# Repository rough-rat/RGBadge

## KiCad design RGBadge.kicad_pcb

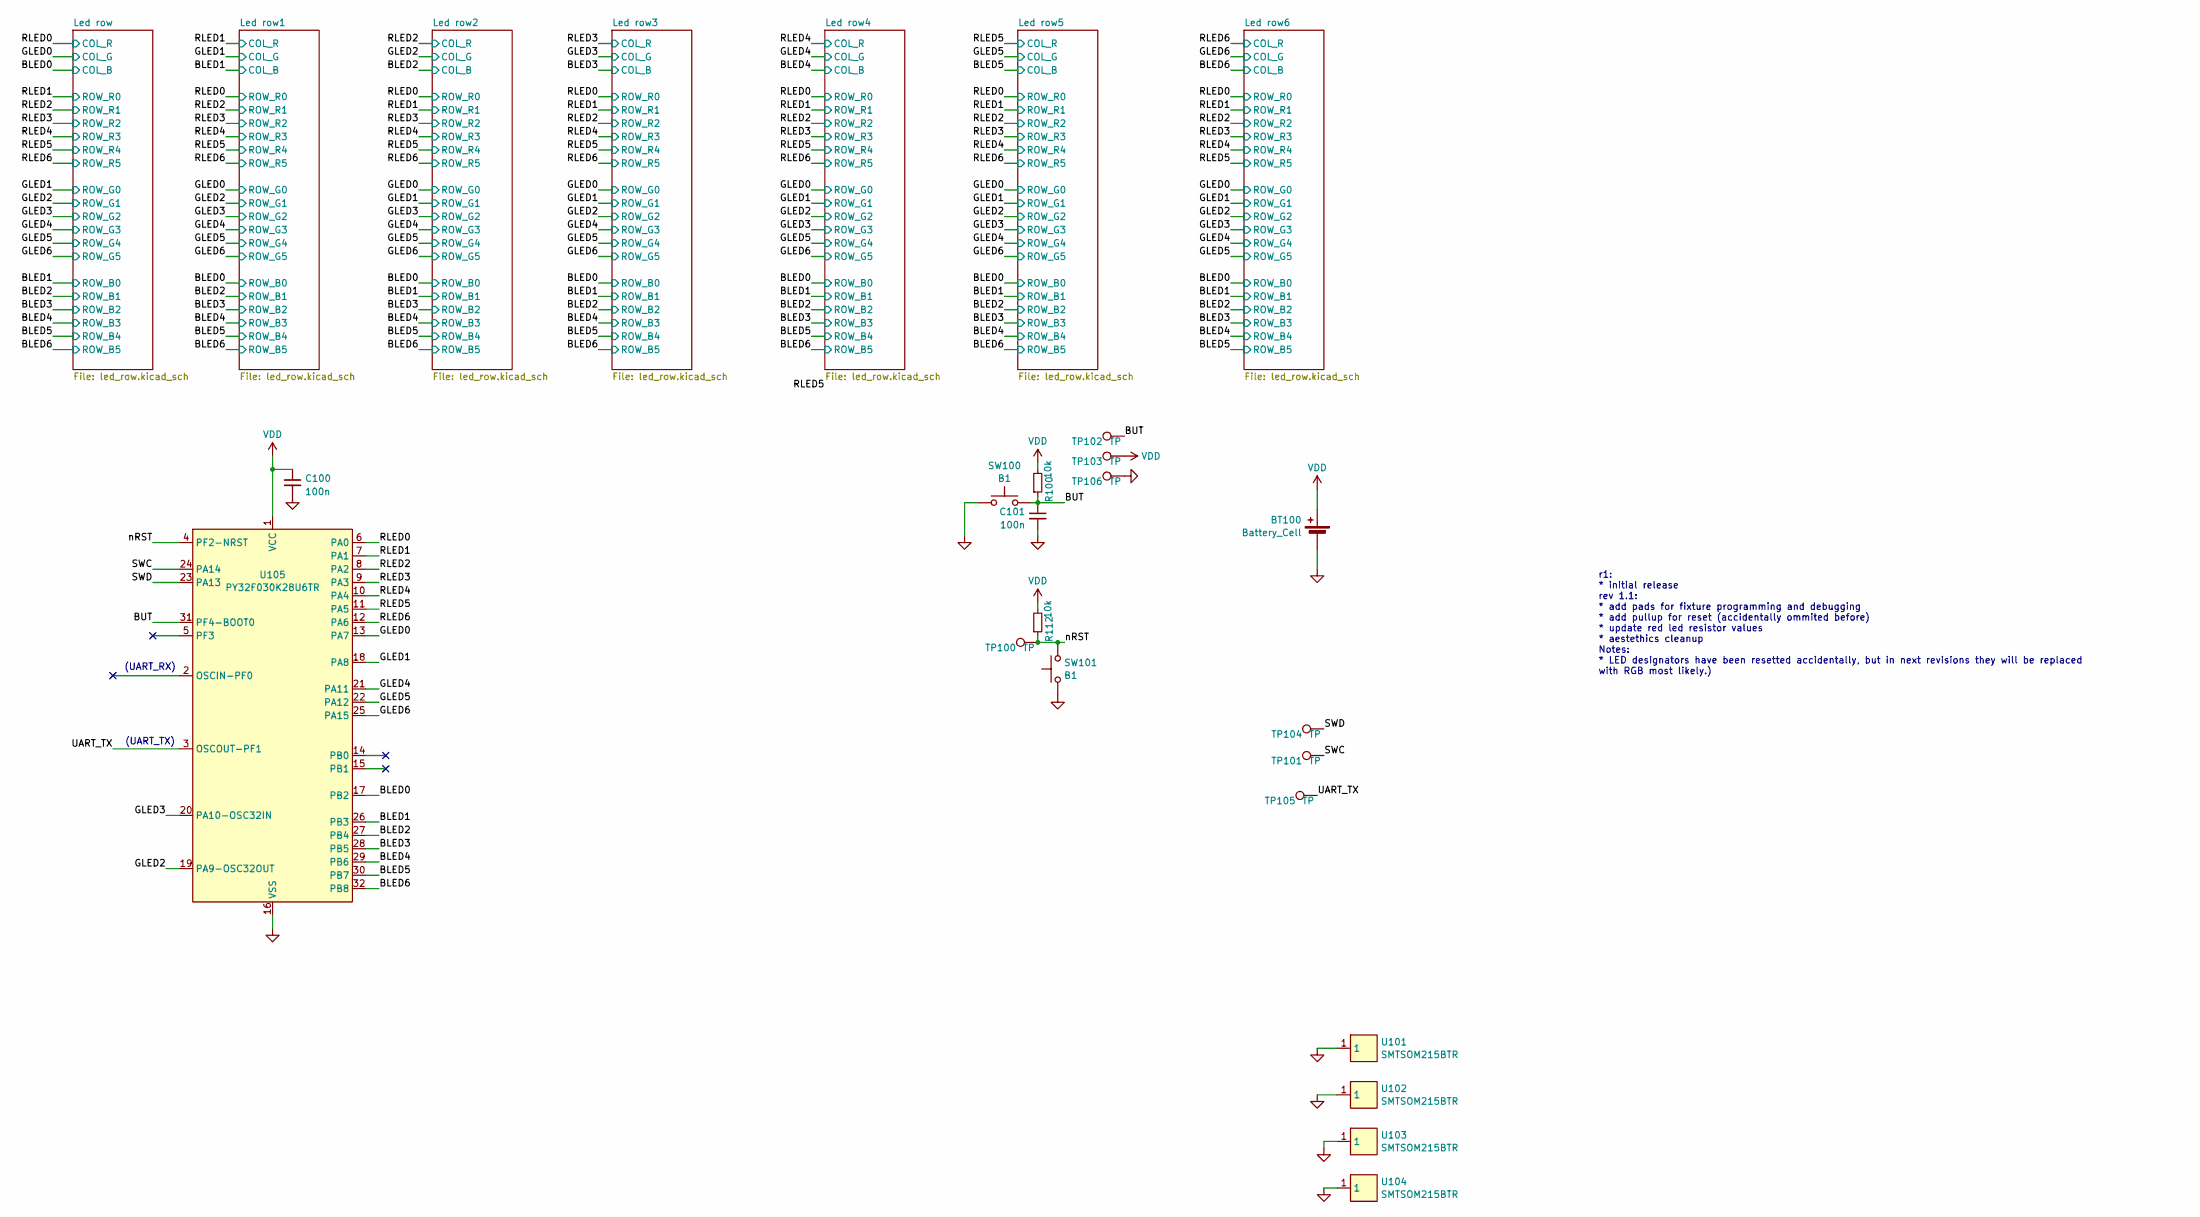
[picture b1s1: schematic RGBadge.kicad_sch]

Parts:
BT100: Battery_Cell; BatteryHolder_Keystone_1060_1x2032; LCSC DNP
C100, C101: 100n; C_0402_1005Metric; LCSC C1525
R100, R112: 10k; R_0402_1005Metric; LCSC C25744
SW100, SW101: B1; SW_SPST_FSMSM; LCSC DNP
TP100, TP101, TP102, TP103, TP104, TP105, TP106: TP; TestPoint_Pad_D1.0mm; LCSC DNP
U101, U102, U103, U104: SMTSOM215BTR; SMD_BD5.6-D3.6; LCSC C5301777
U105: PY32F030K28U6TR; QFN-32_L5.0-W5.0-P0.50-TL-EP3.5; LCSC Part C3018718

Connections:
/BLED0: U105.17 (PB2); also elsewhere on the board
/BLED1: U105.26 (PB3); also elsewhere on the board
/BLED2: U105.27 (PB4); also elsewhere on the board
/BLED3: U105.28 (PB5); also elsewhere on the board
/BLED4: U105.29 (PB6); also elsewhere on the board
/BLED5: U105.30 (PB7); also elsewhere on the board
/BLED6: U105.32 (PB8); also elsewhere on the board
/BUT: C101.1, R100.1, SW100.2, TP102.1 (1_1), U105.31 (PF4-BOOT0)
/GLED0: U105.13 (PA7); also elsewhere on the board
/GLED1: U105.18 (PA8); also elsewhere on the board
/GLED2: U105.19 (PA9-OSC32OUT); also elsewhere on the board
/GLED3: U105.20 (PA10-OSC32IN); also elsewhere on the board
/GLED4: U105.21 (PA11); also elsewhere on the board
/GLED5: U105.22 (PA12); also elsewhere on the board
/GLED6: U105.25 (PA15); also elsewhere on the board
/RLED0: U105.6 (PA0); also elsewhere on the board
/RLED1: U105.7 (PA1); also elsewhere on the board
/RLED2: U105.8 (PA2); also elsewhere on the board
/RLED3: U105.9 (PA3); also elsewhere on the board
/RLED4: U105.10 (PA4); also elsewhere on the board
/RLED5: U105.11 (PA5); also elsewhere on the board
/RLED6: U105.12 (PA6); also elsewhere on the board
/SWC: TP101.1 (1_1), U105.24 (PA14)
/SWD: TP104.1 (1_1), U105.23 (PA13)
/UART_TX: TP105.1 (1_1), U105.3 (OSCOUT-PF1)
/nRST: R112.1, SW101.2, TP100.1 (1_1), U105.4 (PF2-NRST)
GND: BT100.2 (-), C100.2, C101.2, SW100.1, SW101.1, TP106.1 (1_1), U101.1 (1_1), U102.1 (1_1), U103.1 (1_1), U104.1 (1_1), U105.16 (VSS), U105.33 (VSS)
VDD: BT100.1 (+), C100.1, R100.2, R112.2, TP103.1 (1_1), U105.1 (VCC)

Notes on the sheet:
(UART_RX)
(UART_TX)
r1: * initial release rev 1.1: * add pads for fixture programming and debugging * add pullup for reset (accidentally ommited before) * update red led resistor values * aestethics cleanup Notes: * LED designators have been resetted accidentally, but in next revisions they will be replaced with RGB m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

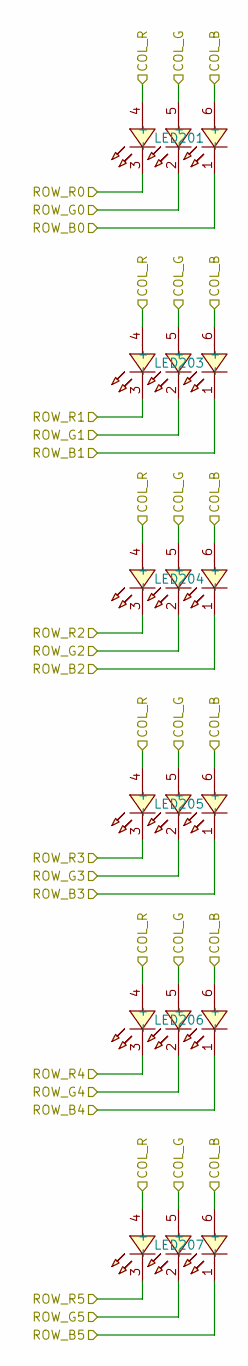
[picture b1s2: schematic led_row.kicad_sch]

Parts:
LED201, LED203, LED204, LED205, LED206, LED207: FM-Z2727RGBA-SH; LED-SMD_6P-L2.7-W2.8-TL; LCSC Part C727905

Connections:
/BLED0: LED201.6 (+), LED203.6 (+), LED204.6 (+), LED205.6 (+), LED206.6 (+), LED207.6 (+); also elsewhere on the board
/BLED1: LED201.1 (-); also elsewhere on the board
/BLED2: LED203.1 (-); also elsewhere on the board
/BLED3: LED204.1 (-); also elsewhere on the board
/BLED4: LED205.1 (-); also elsewhere on the board
/BLED5: LED206.1 (-); also elsewhere on the board
/BLED6: LED207.1 (-); also elsewhere on the board
/GLED0: LED201.5 (+), LED203.5 (+), LED204.5 (+), LED205.5 (+), LED206.5 (+), LED207.5 (+); also elsewhere on the board
/GLED1: LED201.2 (-); also elsewhere on the board
/GLED2: LED203.2 (-); also elsewhere on the board
/GLED3: LED204.2 (-); also elsewhere on the board
/GLED4: LED205.2 (-); also elsewhere on the board
/GLED5: LED206.2 (-); also elsewhere on the board
/GLED6: LED207.2 (-); also elsewhere on the board
/RLED0: LED201.4 (+), LED203.4 (+), LED204.4 (+), LED205.4 (+), LED206.4 (+), LED207.4 (+); also elsewhere on the board
/RLED1: LED201.3 (-); also elsewhere on the board
/RLED2: LED203.3 (-); also elsewhere on the board
/RLED3: LED204.3 (-); also elsewhere on the board
/RLED4: LED205.3 (-); also elsewhere on the board
/RLED5: LED206.3 (-); also elsewhere on the board
/RLED6: LED207.3 (-); also elsewhere on the board

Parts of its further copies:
LED301, LED302, LED303, LED304, LED305, LED306, LED307, LED308, LED309, LED310, LED311, LED312, LED313, LED314, LED315, LED316, LED317, LED318, LED601, LED602, LED603, LED604, LED605, LED606, LED607, LED608, LED609, LED610, LED611, LED612, LED701, LED702, LED703, LED704, LED705, LED706: FM-Z2727RGBA-SH; LED-SMD_6P-L2.7-W2.8-TL; LCSC Part C727905

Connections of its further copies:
/BLED0: LED301.1 (-), LED307.1 (-), LED313.1 (-), LED601.1 (-), LED607.1 (-), LED701.1 (-); also elsewhere on the board
/BLED1: LED301.6 (+), LED302.6 (+), LED303.6 (+), LED304.6 (+), LED305.6 (+), LED306.6 (+), LED308.1 (-), LED314.1 (-), LED602.1 (-), LED608.1 (-), LED702.1 (-); also elsewhere on the board
/BLED2: LED302.1 (-), LED307.6 (+), LED308.6 (+), LED309.6 (+), LED310.6 (+), LED311.6 (+), LED312.6 (+), LED315.1 (-), LED603.1 (-), LED609.1 (-), LED703.1 (-); also elsewhere on the board
/BLED3: LED303.1 (-), LED309.1 (-), LED313.6 (+), LED314.6 (+), LED315.6 (+), LED316.6 (+), LED317.6 (+), LED318.6 (+), LED604.1 (-), LED610.1 (-), LED704.1 (-); also elsewhere on the board
/BLED4: LED304.1 (-), LED310.1 (-), LED316.1 (-), LED601.6 (+), LED602.6 (+), LED603.6 (+), LED604.6 (+), LED605.6 (+), LED606.6 (+), LED611.1 (-), LED705.1 (-); also elsewhere on the board
/BLED5: LED305.1 (-), LED311.1 (-), LED317.1 (-), LED605.1 (-), LED607.6 (+), LED608.6 (+), LED609.6 (+), LED610.6 (+), LED611.6 (+), LED612.6 (+), LED706.1 (-); also elsewhere on the board
/BLED6: LED306.1 (-), LED312.1 (-), LED318.1 (-), LED606.1 (-), LED612.1 (-), LED701.6 (+), LED702.6 (+), LED703.6 (+), LED704.6 (+), LED705.6 (+), LED706.6 (+); also elsewhere on the board
/GLED0: LED301.2 (-), LED307.2 (-), LED313.2 (-), LED601.2 (-), LED607.2 (-), LED701.2 (-); also elsewhere on the board
/GLED1: LED301.5 (+), LED302.5 (+), LED303.5 (+), LED304.5 (+), LED305.5 (+), LED306.5 (+), LED308.2 (-), LED314.2 (-), LED602.2 (-), LED608.2 (-), LED702.2 (-); also elsewhere on the board
/GLED2: LED302.2 (-), LED307.5 (+), LED308.5 (+), LED309.5 (+), LED310.5 (+), LED311.5 (+), LED312.5 (+), LED315.2 (-), LED603.2 (-), LED609.2 (-), LED703.2 (-); also elsewhere on the board
/GLED3: LED303.2 (-), LED309.2 (-), LED313.5 (+), LED314.5 (+), LED315.5 (+), LED316.5 (+), LED317.5 (+), LED318.5 (+), LED604.2 (-), LED610.2 (-), LED704.2 (-); also elsewhere on the board
/GLED4: LED304.2 (-), LED310.2 (-), LED316.2 (-), LED601.5 (+), LED602.5 (+), LED603.5 (+), LED604.5 (+), LED605.5 (+), LED606.5 (+), LED611.2 (-), LED705.2 (-); also elsewhere on the board
/GLED5: LED305.2 (-), LED311.2 (-), LED317.2 (-), LED605.2 (-), LED607.5 (+), LED608.5 (+), LED609.5 (+), LED610.5 (+), LED611.5 (+), LED612.5 (+), LED706.2 (-); also elsewhere on the board
/GLED6: LED306.2 (-), LED312.2 (-), LED318.2 (-), LED606.2 (-), LED612.2 (-), LED701.5 (+), LED702.5 (+), LED703.5 (+), LED704.5 (+), LED705.5 (+), LED706.5 (+); also elsewhere on the board
/RLED0: LED301.3 (-), LED307.3 (-), LED313.3 (-), LED601.3 (-), LED607.3 (-), LED701.3 (-); also elsewhere on the board
/RLED1: LED301.4 (+), LED302.4 (+), LED303.4 (+), LED304.4 (+), LED305.4 (+), LED306.4 (+), LED308.3 (-), LED314.3 (-), LED602.3 (-), LED608.3 (-), LED702.3 (-); also elsewhere on the board
/RLED2: LED302.3 (-), LED307.4 (+), LED308.4 (+), LED309.4 (+), LED310.4 (+), LED311.4 (+), LED312.4 (+), LED315.3 (-), LED603.3 (-), LED609.3 (-), LED703.3 (-); also elsewhere on the board
/RLED3: LED303.3 (-), LED309.3 (-), LED313.4 (+), LED314.4 (+), LED315.4 (+), LED316.4 (+), LED317.4 (+), LED318.4 (+), LED604.3 (-), LED610.3 (-), LED704.3 (-); also elsewhere on the board
/RLED4: LED304.3 (-), LED310.3 (-), LED316.3 (-), LED601.4 (+), LED602.4 (+), LED603.4 (+), LED604.4 (+), LED605.4 (+), LED606.4 (+), LED611.3 (-), LED705.3 (-); also elsewhere on the board
/RLED5: LED305.3 (-), LED311.3 (-), LED317.3 (-), LED605.3 (-), LED607.4 (+), LED608.4 (+), LED609.4 (+), LED610.4 (+), LED611.4 (+), LED612.4 (+), LED706.3 (-); also elsewhere on the board
/RLED6: LED306.3 (-), LED312.3 (-), LED318.3 (-), LED606.3 (-), LED612.3 (-), LED701.4 (+), LED702.4 (+), LED703.4 (+), LED704.4 (+), LED705.4 (+), LED706.4 (+); also elsewhere on the board

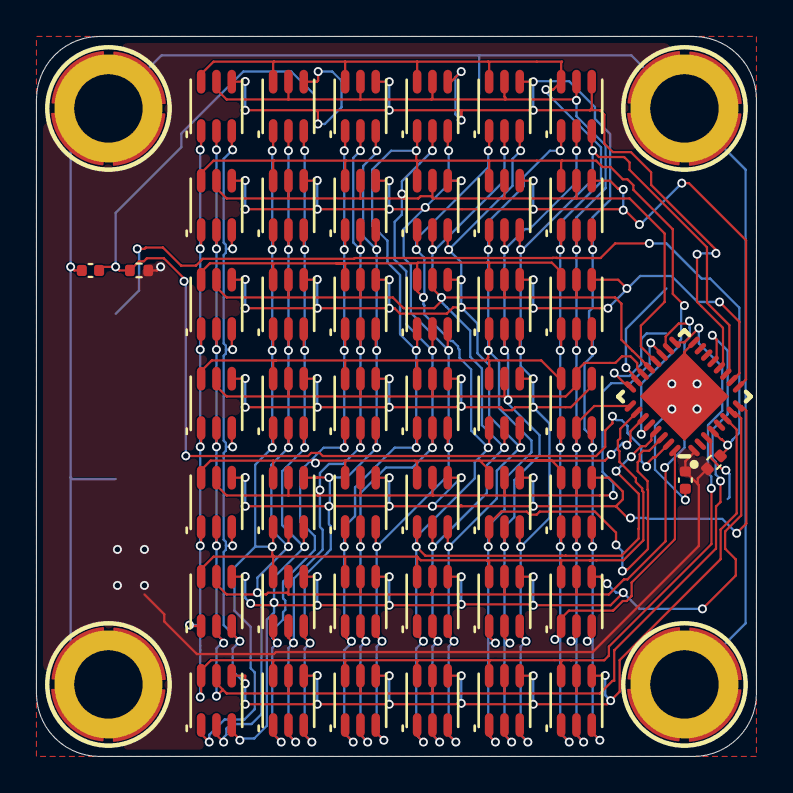
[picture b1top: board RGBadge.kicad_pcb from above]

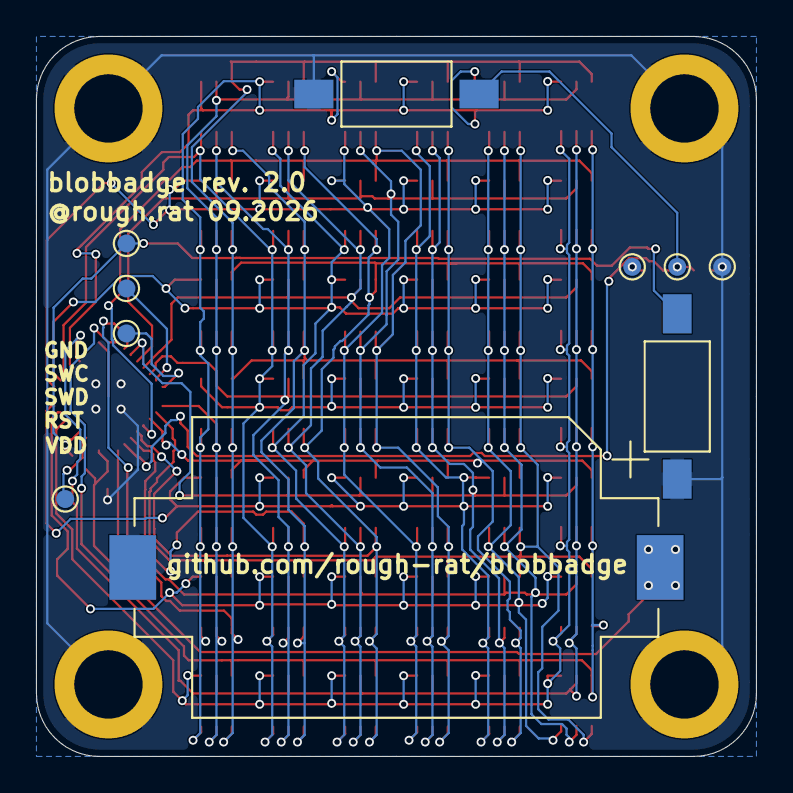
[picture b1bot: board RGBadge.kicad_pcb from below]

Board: 2 copper layers, 40.0 x 40.0 mm, 61 parts (10 on the bottom side), 28 nets.

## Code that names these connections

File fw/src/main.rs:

//! RGBadge: 6x7 RGB LED matrix, one 7-pin charlieplex per colour, and one
//! button (BUT) that turns the badge off and on.

#![no_std]
#![no_main]
#![feature(impl_trait_in_assoc_type)]

use cortex_m::peripheral::SCB;
use cortex_m_rt::{exception, ExceptionFrame};
use defmt::*;
use embassy_executor::Spawner;
use embassy_time::{Duration, Instant};

use py32_badgekit::button::Button;
use py32_badgekit::charlieplex::{self, Led};
use py32_badgekit::power::{self, WakePin};
use py32_badgekit::{font, Port};
use py32_hal::gpio::{Input, Pull};
use py32_hal::rcc::Sysclk;
use py32_hal::time::Hertz;
use {defmt_rtt as _, panic_halt as _};

// ---- Board -----------------------------------------------------------------

const SYSCLK_HZ: u32 = 24_000_000;

/// 42 slots * 100us = 4.2ms -> ~238Hz refresh.
const SLOT_US: u32 = 100;

const WIDTH: usize = 6;
const HEIGHT: usize = 7;
const PIXELS: usize = WIDTH * HEIGHT;

const RED: usize = 0;
const GREEN: usize = 1;
const BLUE: usize = 2;
const COLORS: usize = 3;

/// Charlieplex pins, index = net number (xLED0..xLED6).
const RED_PINS: [u8; 7] = [0, 1, 2, 3, 4, 5, 6]; // PA
const GREEN_PINS: [u8; 7] = [7, 8, 9, 10, 11, 12, 15]; // PA
const BLUE_PINS: [u8; 7] = [2, 3, 4, 5, 6, 7, 8]; // PB

/// Each net is the anode of one physical row (6 LEDs), whose cathodes walk
/// through the other nets left to right. Anode net of row `y`, row 0 is the
/// top one.
const ROW_NET: [usize; HEIGHT] = [6, 3, 4, 5, 2, 1, 0];

/// One colour's matrix in screen order: LED `y * WIDTH + x`.
const fn matrix(port: Port, pins: &[u8; 7]) -> [Led; PIXELS] {
    let mut leds = [Led::new(port, pins[0], pins[1]); PIXELS];
    let mut i = 0;
    while i < PIXELS {
        let (x, y) = (i % WIDTH, i / WIDTH);
        leds[i] = Led::canonical(port, pins, ROW_NET[y] * WIDTH + x);
        i += 1;
    }
    leds
}

static RED_LEDS: [Led; PIXELS] = matrix(Port::A, &RED_PINS);
static GREEN_LEDS: [Led; PIXELS] = matrix(Port::A, &GREEN_PINS);
static BLUE_LEDS: [Led; PIXELS] = matrix(Port::B, &BLUE_PINS);

/// LED index = `color * PIXELS + y * WIDTH + x`.
static LED_GROUPS: [&[Led]; COLORS] = [&RED_LEDS, &GREEN_LEDS, &BLUE_LEDS];

/// BUT (SW100) on PF4/BOOT0, to ground.
const WAKE: WakePin = WakePin::new(Port::F, 4);

/// Sets a whole column of one colour, bit `y` of `bits` = row `y` (bit 0 is
/// the top row).
fn set_column(color: usize, x: usize, bits: u8) {
    for y in 0..HEIGHT {
        charlieplex::set(color * PIXELS + y * WIDTH + x, bits & (1 << y) != 0);
    }
}

/// Sets a whole column, `rgb` is a bitmask of the colours to light
/// (bit `RED`, `GREEN`, `BLUE`).
fn set_column_rgb(rgb: u8, x: usize, bits: u8) {
    for color in 0..COLORS {
        set_column(color, x, if rgb & (1 << color) != 0 { bits } else { 0 });
    }
}

// ---- Behaviour -------------------------------------------------------------

const MESSAGE: &[u8] = b"HELLO WORLD";

/// The badge turns itself off after this long without a button press.
const AWAKE_TIMEOUT: Duration = Duration::from_secs(10 * 60);

const WIPE_STEP: Duration = Duration::from_millis(40);
const SCROLL_STEP: Duration = Duration::from_millis(70);

/// Reason an animation ended early: button pressed or awake time used up.
struct Off;

struct Show<'a, 'd> {
    button: &'a mut Button<'d>,
    deadline: Instant,
}

impl Show<'_, '_> {
    /// Delay between animation steps.
    async fn step(&mut self, duration: Duration) -> Result<(), Off> {
        if self.button.pressed_within(duration).await || Instant::now() >= self.deadline {
            Err(Off)
        } else {
            Ok(())
        }
    }

    /// Fills the matrix column by column in each colour, then empties it the
    /// same way. Lights every LED die once, so it doubles as an assembly
    /// check.
    async fn wipe(&mut self) -> Result<(), Off> {
        for color in [RED, GREEN, BLUE] {
            for bits in [0x7F, 0x00] {
                for x in 0..WIDTH {
                    set_column(color, x, bits);
                    self.step(WIPE_STEP).await?;
                }
            }
        }
        Ok(())
    }

    /// Scrolls the message in from the right edge and out over the left one.
    async fn scroll_message(&mut self, rgb: u8) -> Result<(), Off> {
        let message_cols = font::text_width(MESSAGE);

        for offset in 0..message_cols + WIDTH {
            for x in 0..WIDTH {
                // The message starts one screen width to the right.
                let bits = match (offset + x).checked_sub(WIDTH) {
                    Some(i) if i < message_cols => font::text_column(MESSAGE, i),
                    _ => 0,
                };
                set_column_rgb(rgb, x, bits);
            }
            self.step(SCROLL_STEP).await?;
        }
        Ok(())
    }

    async fn run(&mut self) -> Result<(), Off> {
        loop {
            // Every colour mix but black: R, G, R+G, B, ...
            for rgb in 1..8 {
                self.wipe().await?;
                self.scroll_message(rgb).await?;
                charlieplex::clear();
            }
        }
    }
}

#[embassy_executor::main]
async fn main(_spawner: Spawner) {
    // Recovery window: stay awake with every pin in its reset state for a
    // second or two (HSI reset default, before any clock setup), so a probe
    // can always attach right after power-up even if the code below ever
    // breaks SWD or sleeps too deep. Keep this first.
    cortex_m::asm::delay(8_000_000);

    let mut cfg: py32_hal::Config = Default::default();
    cfg.rcc.hsi = Some(Hertz::mhz(SYSCLK_HZ / 1_000_000));
    cfg.rcc.sys = Sysclk::HSI;
    let p = py32_hal::init(cfg);

    info!("Hello World!");

    // PA13/PA14 (SWD) and PF2 (nRST) are left alone on purpose.
    let syst = cortex_m::Peripherals::take().unwrap().SYST;
    charlieplex::init(syst, SYSCLK_HZ, SLOT_US, &LED_GROUPS);

    // Pulled up on the board as well.
    let mut button = Button::new(Input::new(p.PF4, Pull::Up));

    loop {
        let mut show = Show {
            button: &mut button,
            deadline: Instant::now() + AWAKE_TIMEOUT,
        };
        let _ = show.run().await;

        info!("off");
        charlieplex::stop();
        charlieplex::clear();
        button.wait_release().await;
        power::stop(WAKE);
        button.wait_release().await;
        info!("on");
        charlieplex::start();
    }
}

//conserve flash space with the non-handler
#[exception]
unsafe fn HardFault(_frame: &ExceptionFrame) -> ! {
    SCB::sys_reset()
}
